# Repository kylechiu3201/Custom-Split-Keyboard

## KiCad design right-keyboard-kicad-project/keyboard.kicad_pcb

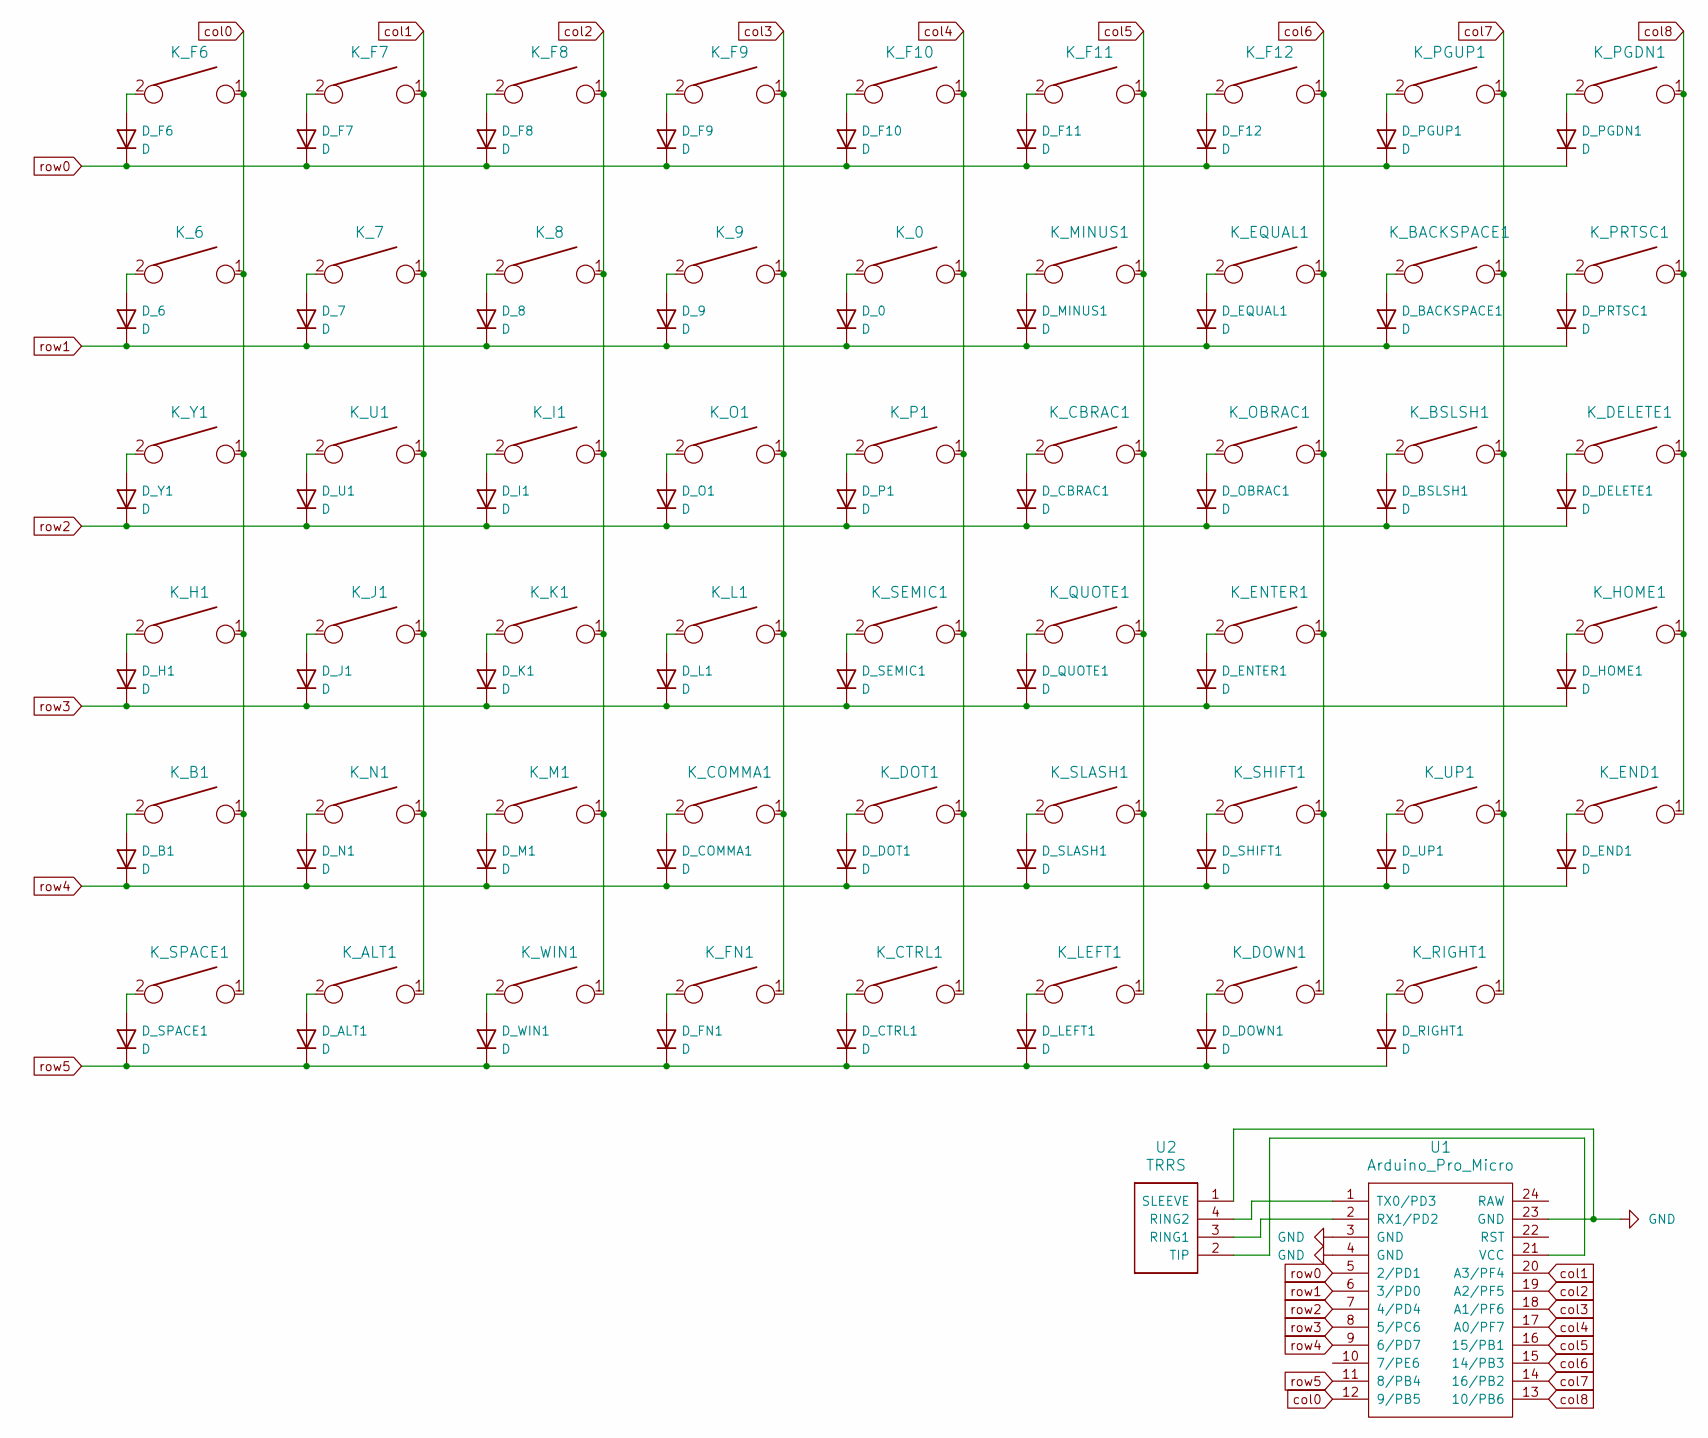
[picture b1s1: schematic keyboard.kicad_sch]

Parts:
D_0, D_6, D_7, D_8, D_9: D; D_SOD123_axial
D_ALT1: D; D_SOD123_axial
D_B1: D; D_SOD123_axial
D_BACKSPACE1: D; D_SOD123_axial
D_BSLSH1: D; D_SOD123_axial
D_CBRAC1: D; D_SOD123_axial
D_COMMA1: D; D_SOD123_axial
D_CTRL1: D; D_SOD123_axial
D_DELETE1: D; D_SOD123_axial
D_DOT1: D; D_SOD123_axial
D_DOWN1: D; D_SOD123_axial
D_END1: D; D_SOD123_axial
D_ENTER1: D; D_SOD123_axial
D_EQUAL1: D; D_SOD123_axial
D_F6, D_F7, D_F8, D_F9, D_F10, D_F11, D_F12: D; D_SOD123_axial
D_FN1: D; D_SOD123_axial
D_H1: D; D_SOD123_axial
D_HOME1: D; D_SOD123_axial
D_I1: D; D_SOD123_axial
D_J1: D; D_SOD123_axial
D_K1: D; D_SOD123_axial
D_L1: D; D_SOD123_axial
D_LEFT1: D; D_SOD123_axial
D_M1: D; D_SOD123_axial
D_MINUS1: D; D_SOD123_axial
D_N1: D; D_SOD123_axial
D_O1: D; D_SOD123_axial
D_OBRAC1: D; D_SOD123_axial
D_P1: D; D_SOD123_axial
D_PGDN1: D; D_SOD123_axial
D_PGUP1: D; D_SOD123_axial
D_PRTSC1: D; D_SOD123_axial
D_QUOTE1: D; D_SOD123_axial
D_RIGHT1: D; D_SOD123_axial
D_SEMIC1: D; D_SOD123_axial
D_SHIFT1: D; D_SOD123_axial
D_SLASH1: D; D_SOD123_axial
D_SPACE1: D; D_SOD123_axial
D_U1: D; D_SOD123_axial
D_UP1: D; D_SOD123_axial
D_WIN1: D; D_SOD123_axial
D_Y1: D; D_SOD123_axial
K_0, K_6, K_7, K_8, K_9: KEYSW; MXOnly-1U-Hotswap
K_ALT1: KEYSW; MXOnly-1U-Hotswap
K_B1: KEYSW; MXOnly-1U-Hotswap
K_BACKSPACE1: KEYSW; MXOnly-2U-Hotswap
K_BSLSH1: KEYSW; MXOnly-1.5U-Hotswap
K_CBRAC1: KEYSW; MXOnly-1U-Hotswap
K_COMMA1: KEYSW; MXOnly-1U-Hotswap
K_CTRL1: KEYSW; MXOnly-1U-Hotswap
K_DELETE1: KEYSW; MXOnly-1U-Hotswap
K_DOT1: KEYSW; MXOnly-1U-Hotswap
K_DOWN1: KEYSW; MXOnly-1U-Hotswap
K_END1: KEYSW; MXOnly-1U-Hotswap
K_ENTER1: KEYSW; MXOnly-2.25U-Hotswap
K_EQUAL1: KEYSW; MXOnly-1U-Hotswap
K_F6, K_F7, K_F8, K_F9, K_F10, K_F11, K_F12: KEYSW; MXOnly-1U-Hotswap
K_FN1: KEYSW; MXOnly-1U-Hotswap
K_H1: KEYSW; MXOnly-1U-Hotswap
K_HOME1: KEYSW; MXOnly-1U-Hotswap
K_I1: KEYSW; MXOnly-1U-Hotswap
K_J1: KEYSW; MXOnly-1U-Hotswap
K_K1: KEYSW; MXOnly-1U-Hotswap
K_L1: KEYSW; MXOnly-1U-Hotswap
K_LEFT1: KEYSW; MXOnly-1U-Hotswap
K_M1: KEYSW; MXOnly-1U-Hotswap
K_MINUS1: KEYSW; MXOnly-1U-Hotswap
K_N1: KEYSW; MXOnly-1U-Hotswap
K_O1: KEYSW; MXOnly-1U-Hotswap
K_OBRAC1: KEYSW; MXOnly-1U-Hotswap
K_P1: KEYSW; MXOnly-1U-Hotswap
K_PGDN1: KEYSW; MXOnly-1U-Hotswap
K_PGUP1: KEYSW; MXOnly-1U-Hotswap
K_PRTSC1: KEYSW; MXOnly-1U-Hotswap
K_QUOTE1: KEYSW; MXOnly-1U-Hotswap
K_RIGHT1: KEYSW; MXOnly-1U-Hotswap
K_SEMIC1: KEYSW; MXOnly-1U-Hotswap
K_SHIFT1: KEYSW; MXOnly-1.75U-Hotswap
K_SLASH1: KEYSW; MXOnly-1U-Hotswap
K_SPACE1: KEYSW; MXOnly-2.25U-Hotswap
K_U1: KEYSW; MXOnly-1U-Hotswap
K_UP1: KEYSW; MXOnly-1U-Hotswap
K_WIN1: KEYSW; MXOnly-1U-Hotswap
K_Y1: KEYSW; MXOnly-1U-Hotswap
U1: Arduino_Pro_Micro
U2: TRRS; TRRS_PJ-320A

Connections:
GND: U1.3 (GND), U1.4 (GND), U1.23 (GND), U2.1 (SLEEVE)
unnamed: D_0.2 (A), K_0.2
unnamed: D_6.2 (A), K_6.2
unnamed: D_7.2 (A), K_7.2
unnamed: D_8.2 (A), K_8.2
unnamed: D_9.2 (A), K_9.2
unnamed: D_ALT1.2 (A), K_ALT1.2
unnamed: D_B1.2 (A), K_B1.2
unnamed: D_BACKSPACE1.2 (A), K_BACKSPACE1.2
unnamed: D_BSLSH1.2 (A), K_BSLSH1.2
unnamed: D_CBRAC1.2 (A), K_CBRAC1.2
unnamed: D_COMMA1.2 (A), K_COMMA1.2
unnamed: D_CTRL1.2 (A), K_CTRL1.2
unnamed: D_DELETE1.2 (A), K_DELETE1.2
unnamed: D_DOT1.2 (A), K_DOT1.2
unnamed: D_DOWN1.2 (A), K_DOWN1.2
unnamed: D_END1.2 (A), K_END1.2
unnamed: D_ENTER1.2 (A), K_ENTER1.2
unnamed: D_EQUAL1.2 (A), K_EQUAL1.2
unnamed: D_F6.2 (A), K_F6.2
unnamed: D_F7.2 (A), K_F7.2
unnamed: D_F8.2 (A), K_F8.2
unnamed: D_F9.2 (A), K_F9.2
unnamed: D_F10.2 (A), K_F10.2
unnamed: D_F11.2 (A), K_F11.2
unnamed: D_F12.2 (A), K_F12.2
unnamed: D_FN1.2 (A), K_FN1.2
unnamed: D_H1.2 (A), K_H1.2
unnamed: D_HOME1.2 (A), K_HOME1.2
unnamed: D_I1.2 (A), K_I1.2
unnamed: D_J1.2 (A), K_J1.2
unnamed: D_K1.2 (A), K_K1.2
unnamed: D_L1.2 (A), K_L1.2
unnamed: D_LEFT1.2 (A), K_LEFT1.2
unnamed: D_M1.2 (A), K_M1.2
unnamed: D_MINUS1.2 (A), K_MINUS1.2
unnamed: D_N1.2 (A), K_N1.2
unnamed: D_O1.2 (A), K_O1.2
unnamed: D_OBRAC1.2 (A), K_OBRAC1.2
unnamed: D_P1.2 (A), K_P1.2
unnamed: D_PGDN1.2 (A), K_PGDN1.2
unnamed: D_PGUP1.2 (A), K_PGUP1.2
unnamed: D_PRTSC1.2 (A), K_PRTSC1.2
unnamed: D_QUOTE1.2 (A), K_QUOTE1.2
unnamed: D_RIGHT1.2 (A), K_RIGHT1.2
unnamed: D_SEMIC1.2 (A), K_SEMIC1.2
unnamed: D_SHIFT1.2 (A), K_SHIFT1.2
unnamed: D_SLASH1.2 (A), K_SLASH1.2
unnamed: D_SPACE1.2 (A), K_SPACE1.2
unnamed: D_U1.2 (A), K_U1.2
unnamed: D_UP1.2 (A), K_UP1.2
unnamed: D_WIN1.2 (A), K_WIN1.2
unnamed: D_Y1.2 (A), K_Y1.2
unnamed: U1.2 (RX1/PD2), U2.3 (RING1)
unnamed: U1.1 (TX0/PD3), U2.4 (RING2)
unnamed: U1.21 (VCC), U2.2 (TIP)
col0: K_6.1, K_B1.1, K_F6.1, K_H1.1, K_SPACE1.1, K_Y1.1, U1.12 (9/PB5)
col1: K_7.1, K_ALT1.1, K_F7.1, K_J1.1, K_N1.1, K_U1.1, U1.20 (A3/PF4)
col2: K_8.1, K_F8.1, K_I1.1, K_K1.1, K_M1.1, K_WIN1.1, U1.19 (A2/PF5)
col3: K_9.1, K_COMMA1.1, K_F9.1, K_FN1.1, K_L1.1, K_O1.1, U1.18 (A1/PF6)
col4: K_0.1, K_CTRL1.1, K_DOT1.1, K_F10.1, K_P1.1, K_SEMIC1.1, U1.17 (A0/PF7)
col5: K_CBRAC1.1, K_F11.1, K_LEFT1.1, K_MINUS1.1, K_QUOTE1.1, K_SLASH1.1, U1.16 (15/PB1)
col6: K_DOWN1.1, K_ENTER1.1, K_EQUAL1.1, K_F12.1, K_OBRAC1.1, K_SHIFT1.1, U1.15 (14/PB3)
col7: K_BACKSPACE1.1, K_BSLSH1.1, K_PGUP1.1, K_RIGHT1.1, K_UP1.1, U1.14 (16/PB2)
col8: K_DELETE1.1, K_END1.1, K_HOME1.1, K_PGDN1.1, K_PRTSC1.1, U1.13 (10/PB6)
row0: D_F6.1 (K), D_F7.1 (K), D_F8.1 (K), D_F9.1 (K), D_F10.1 (K), D_F11.1 (K), D_F12.1 (K), D_PGDN1.1 (K), D_PGUP1.1 (K), U1.5 (2/PD1)
row1: D_0.1 (K), D_6.1 (K), D_7.1 (K), D_8.1 (K), D_9.1 (K), D_BACKSPACE1.1 (K), D_EQUAL1.1 (K), D_MINUS1.1 (K), D_PRTSC1.1 (K), U1.6 (3/PD0)
row2: D_BSLSH1.1 (K), D_CBRAC1.1 (K), D_DELETE1.1 (K), D_I1.1 (K), D_O1.1 (K), D_OBRAC1.1 (K), D_P1.1 (K), D_U1.1 (K), D_Y1.1 (K), U1.7 (4/PD4)
row3: D_ENTER1.1 (K), D_H1.1 (K), D_HOME1.1 (K), D_J1.1 (K), D_K1.1 (K), D_L1.1 (K), D_QUOTE1.1 (K), D_SEMIC1.1 (K), U1.8 (5/PC6)
row4: D_B1.1 (K), D_COMMA1.1 (K), D_DOT1.1 (K), D_END1.1 (K), D_M1.1 (K), D_N1.1 (K), D_SHIFT1.1 (K), D_SLASH1.1 (K), D_UP1.1 (K), U1.9 (6/PD7)
row5: D_ALT1.1 (K), D_CTRL1.1 (K), D_DOWN1.1 (K), D_FN1.1 (K), D_LEFT1.1 (K), D_RIGHT1.1 (K), D_SPACE1.1 (K), D_WIN1.1 (K), U1.11 (8/PB4)

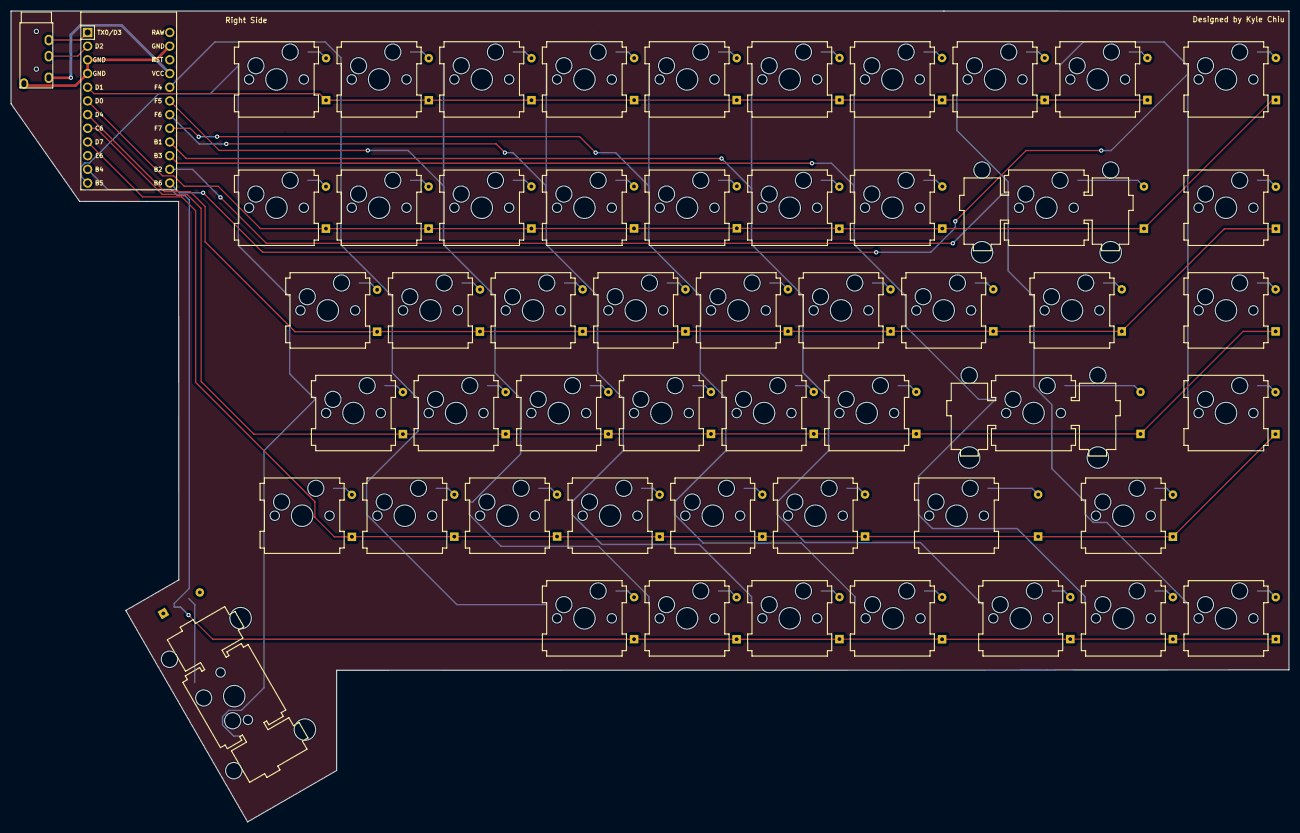
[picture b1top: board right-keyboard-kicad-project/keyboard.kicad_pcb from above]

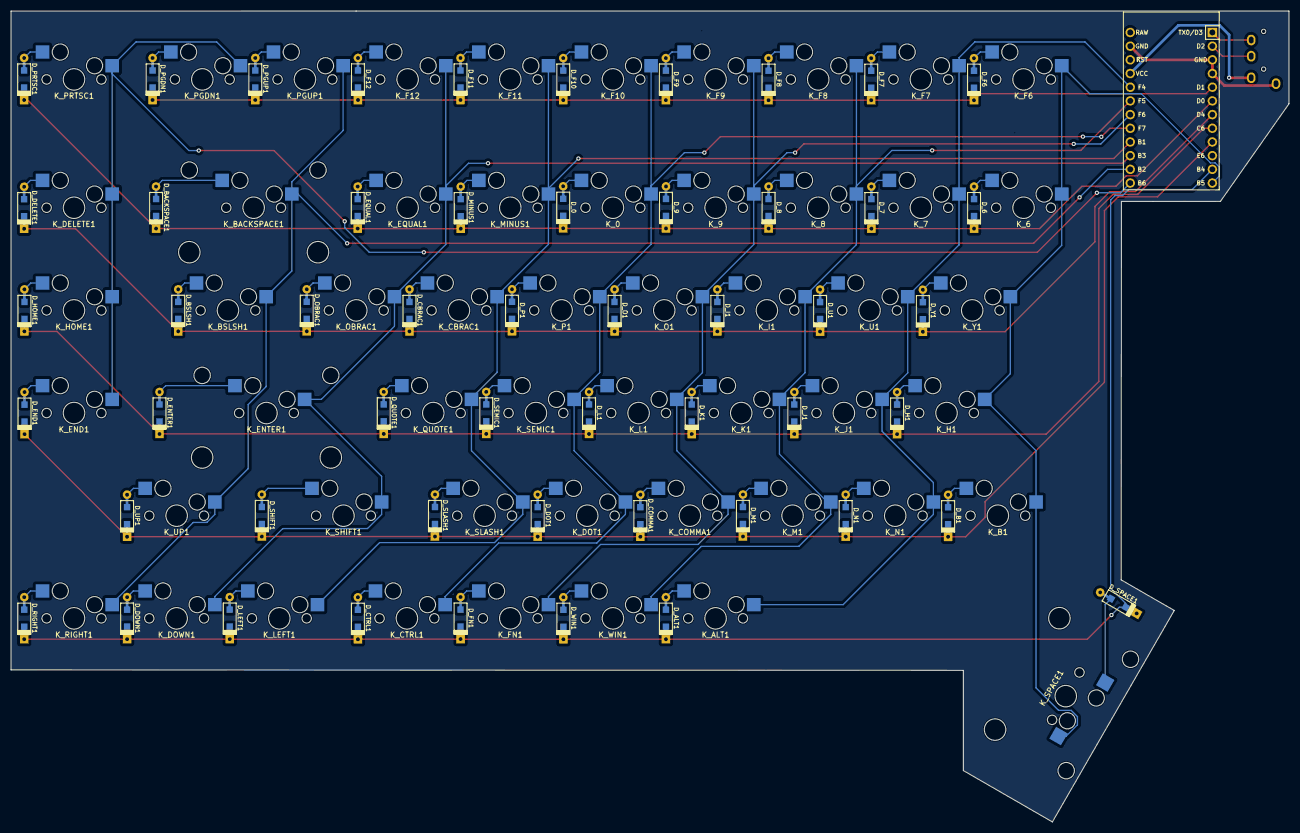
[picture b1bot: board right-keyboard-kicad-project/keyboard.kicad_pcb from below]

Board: 2 copper layers, 237.1 x 150.5 mm, 106 parts (52 on the bottom side), 71 nets.

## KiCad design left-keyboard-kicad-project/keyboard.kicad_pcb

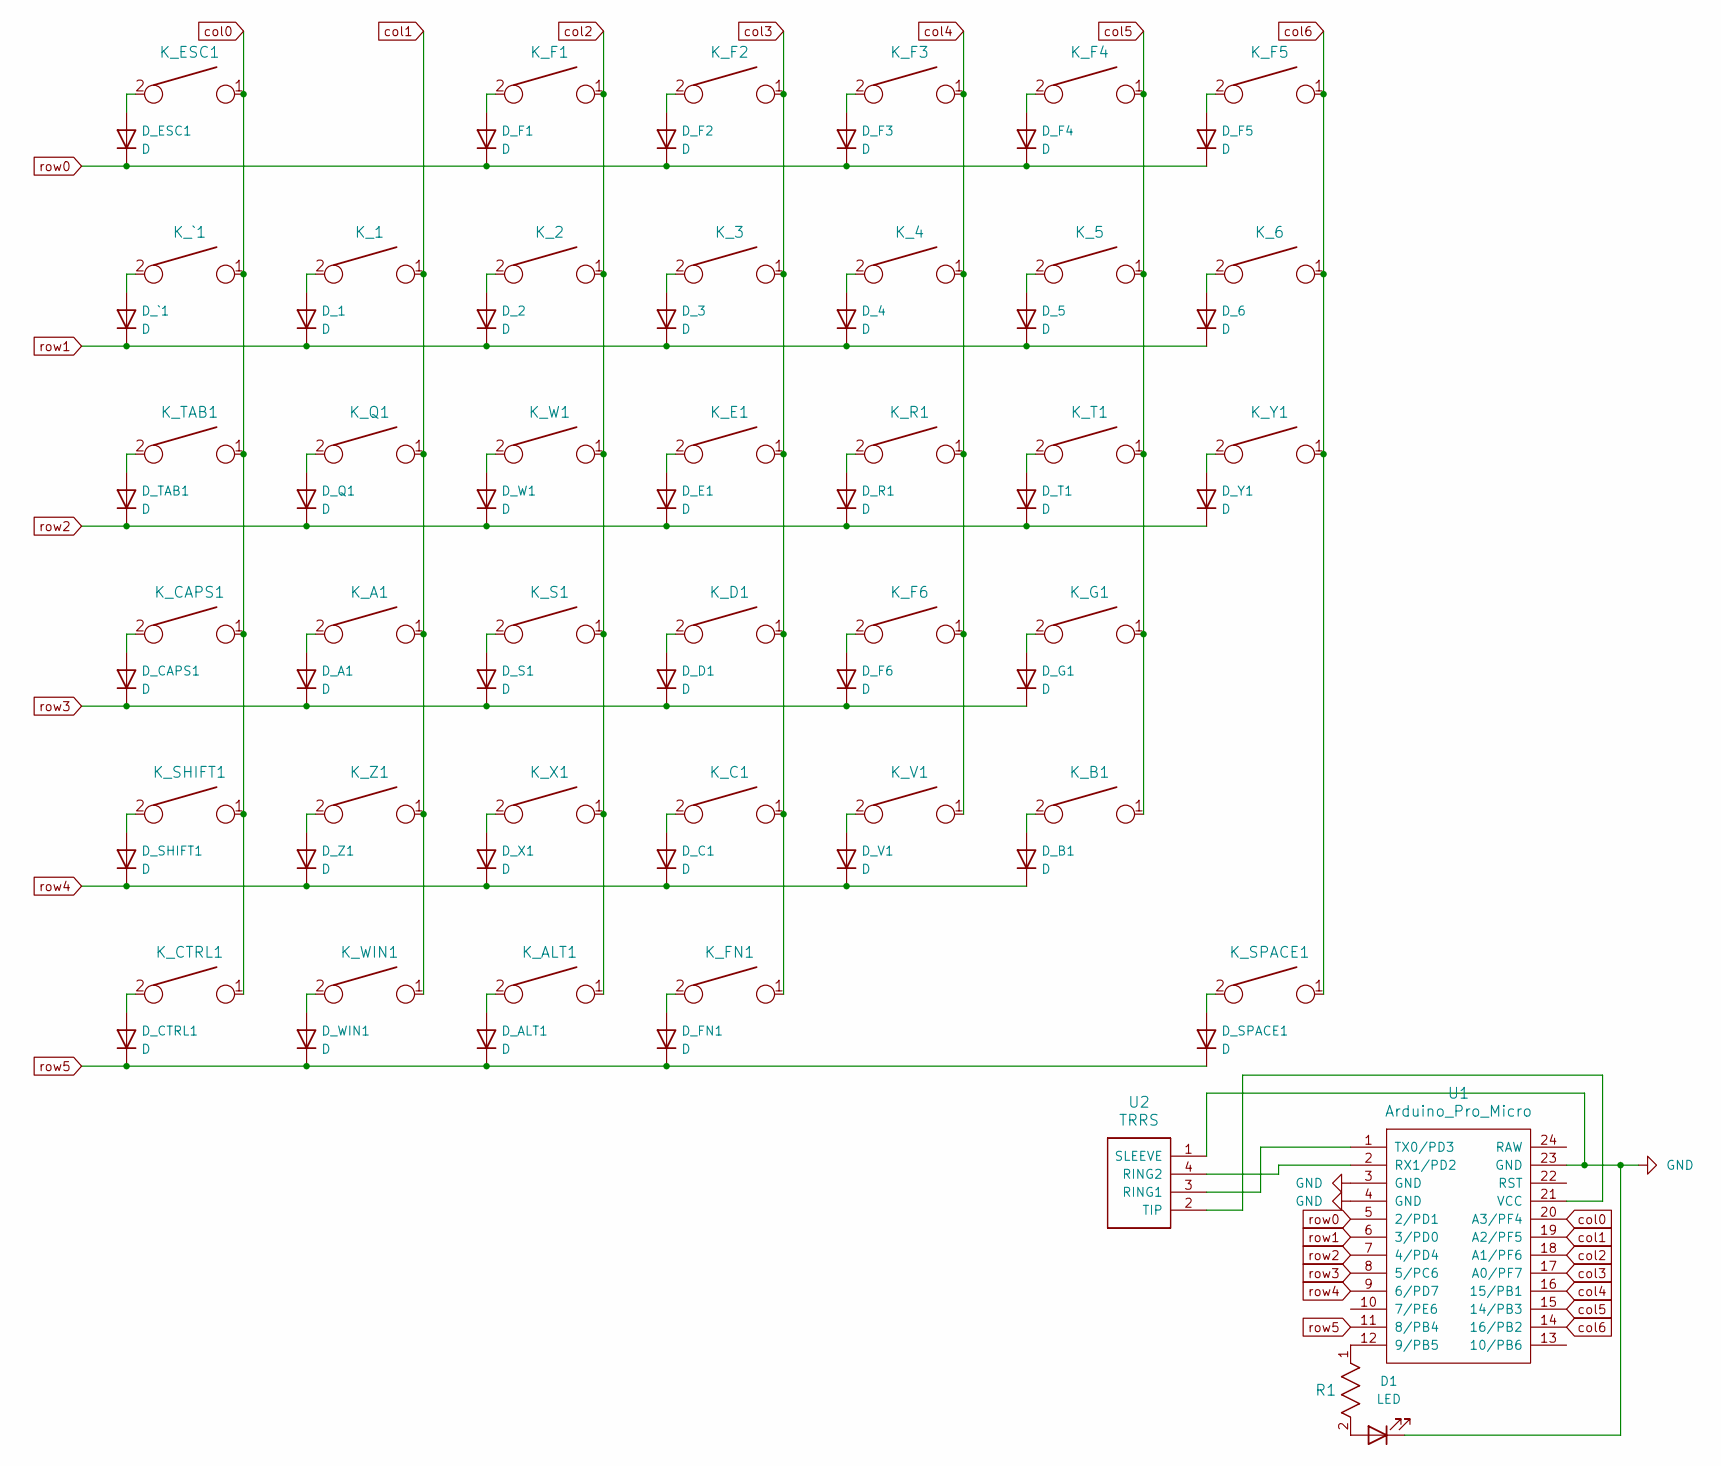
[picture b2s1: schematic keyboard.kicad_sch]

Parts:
D1: LED; LED_CREE_MX6
D_1, D_2, D_3, D_4, D_5, D_6: D; D_SOD123_axial
D_A1: D; D_SOD123_axial
D_ALT1: D; D_SOD123_axial
D_B1: D; D_SOD123_axial
D_C1: D; D_SOD123_axial
D_CAPS1: D; D_SOD123_axial
D_CTRL1: D; D_SOD123_axial
D_D1: D; D_SOD123_axial
D_E1: D; D_SOD123_axial
D_ESC1: D; D_SOD123_axial
D_F1, D_F2, D_F3, D_F4, D_F5, D_F6: D; D_SOD123_axial
D_FN1: D; D_SOD123_axial
D_G1: D; D_SOD123_axial
D_Q1: D; D_SOD123_axial
D_R1: D; D_SOD123_axial
D_S1: D; D_SOD123_axial
D_SHIFT1: D; D_SOD123_axial
D_SPACE1: D; D_SOD123_axial
D_T1: D; D_SOD123_axial
D_TAB1: D; D_SOD123_axial
D_V1: D; D_SOD123_axial
D_W1: D; D_SOD123_axial
D_WIN1: D; D_SOD123_axial
D_X1: D; D_SOD123_axial
D_Y1: D; D_SOD123_axial
D_Z1: D; D_SOD123_axial
D_`1: D; D_SOD123_axial
K_1, K_2, K_3, K_4, K_5, K_6: KEYSW; MXOnly-1U-Hotswap
K_A1: KEYSW; MXOnly-1U-Hotswap
K_ALT1: KEYSW; MXOnly-1.25U-Hotswap
K_B1: KEYSW; MXOnly-1U-Hotswap
K_C1: KEYSW; MXOnly-1U-Hotswap
K_CAPS1: KEYSW; MXOnly-1.75U-Hotswap
K_CTRL1: KEYSW; MXOnly-1.25U-Hotswap
K_D1: KEYSW; MXOnly-1U-Hotswap
K_E1: KEYSW; MXOnly-1U-Hotswap
K_ESC1: KEYSW; MXOnly-1U-Hotswap
K_F1, K_F2, K_F3, K_F4, K_F5, K_F6: KEYSW; MXOnly-1U-Hotswap
K_FN1: KEYSW; MXOnly-1.25U-Hotswap
K_G1: KEYSW; MXOnly-1U-Hotswap
K_Q1: KEYSW; MXOnly-1U-Hotswap
K_R1: KEYSW; MXOnly-1U-Hotswap
K_S1: KEYSW; MXOnly-1U-Hotswap
K_SHIFT1: KEYSW; MXOnly-2.25U-Hotswap
K_SPACE1: KEYSW; MXOnly-2.25U-Hotswap
K_T1: KEYSW; MXOnly-1U-Hotswap
K_TAB1: KEYSW; MXOnly-1.5U-Hotswap
K_V1: KEYSW; MXOnly-1U-Hotswap
K_W1: KEYSW; MXOnly-1U-Hotswap
K_WIN1: KEYSW; MXOnly-1.25U-Hotswap
K_X1: KEYSW; MXOnly-1U-Hotswap
K_Y1: KEYSW; MXOnly-1U-Hotswap
K_Z1: KEYSW; MXOnly-1U-Hotswap
K_`1: KEYSW; MXOnly-1U-Hotswap
R1: R_0805_2012Metric_Pad1.20x1.40mm_HandSolder
U1: Arduino_Pro_Micro
U2: TRRS; TRRS_PJ-320A

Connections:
GND: D1.1 (K), U1.3 (GND), U1.4 (GND), U1.23 (GND), U2.1 (SLEEVE)
unnamed: D1.2 (A), R1.2
unnamed: D_1.2 (A), K_1.2
unnamed: D_2.2 (A), K_2.2
unnamed: D_3.2 (A), K_3.2
unnamed: D_4.2 (A), K_4.2
unnamed: D_5.2 (A), K_5.2
unnamed: D_6.2 (A), K_6.2
unnamed: D_A1.2 (A), K_A1.2
unnamed: D_ALT1.2 (A), K_ALT1.2
unnamed: D_B1.2 (A), K_B1.2
unnamed: D_C1.2 (A), K_C1.2
unnamed: D_CAPS1.2 (A), K_CAPS1.2
unnamed: D_CTRL1.2 (A), K_CTRL1.2
unnamed: D_D1.2 (A), K_D1.2
unnamed: D_E1.2 (A), K_E1.2
unnamed: D_ESC1.2 (A), K_ESC1.2
unnamed: D_F1.2 (A), K_F1.2
unnamed: D_F2.2 (A), K_F2.2
unnamed: D_F3.2 (A), K_F3.2
unnamed: D_F4.2 (A), K_F4.2
unnamed: D_F5.2 (A), K_F5.2
unnamed: D_F6.2 (A), K_F6.2
unnamed: D_FN1.2 (A), K_FN1.2
unnamed: D_G1.2 (A), K_G1.2
unnamed: D_Q1.2 (A), K_Q1.2
unnamed: D_R1.2 (A), K_R1.2
unnamed: D_S1.2 (A), K_S1.2
unnamed: D_SHIFT1.2 (A), K_SHIFT1.2
unnamed: D_SPACE1.2 (A), K_SPACE1.2
unnamed: D_T1.2 (A), K_T1.2
unnamed: D_TAB1.2 (A), K_TAB1.2
unnamed: D_V1.2 (A), K_V1.2
unnamed: D_W1.2 (A), K_W1.2
unnamed: D_WIN1.2 (A), K_WIN1.2
unnamed: D_X1.2 (A), K_X1.2
unnamed: D_Y1.2 (A), K_Y1.2
unnamed: D_Z1.2 (A), K_Z1.2
unnamed: D_`1.2 (A), K_`1.2
unnamed: R1.1, U1.12 (9/PB5)
unnamed: U1.2 (RX1/PD2), U2.4 (RING2)
unnamed: U1.1 (TX0/PD3), U2.3 (RING1)
unnamed: U1.21 (VCC), U2.2 (TIP)
col0: K_CAPS1.1, K_CTRL1.1, K_ESC1.1, K_SHIFT1.1, K_TAB1.1, K_`1.1, U1.20 (A3/PF4)
col1: K_1.1, K_A1.1, K_Q1.1, K_WIN1.1, K_Z1.1, U1.19 (A2/PF5)
col2: K_2.1, K_ALT1.1, K_F1.1, K_S1.1, K_W1.1, K_X1.1, U1.18 (A1/PF6)
col3: K_3.1, K_C1.1, K_D1.1, K_E1.1, K_F2.1, K_FN1.1, U1.17 (A0/PF7)
col4: K_4.1, K_F3.1, K_F6.1, K_R1.1, K_V1.1, U1.16 (15/PB1)
col5: K_5.1, K_B1.1, K_F4.1, K_G1.1, K_T1.1, U1.15 (14/PB3)
col6: K_6.1, K_F5.1, K_SPACE1.1, K_Y1.1, U1.14 (16/PB2)
row0: D_ESC1.1 (K), D_F1.1 (K), D_F2.1 (K), D_F3.1 (K), D_F4.1 (K), D_F5.1 (K), U1.5 (2/PD1)
row1: D_1.1 (K), D_2.1 (K), D_3.1 (K), D_4.1 (K), D_5.1 (K), D_6.1 (K), D_`1.1 (K), U1.6 (3/PD0)
row2: D_E1.1 (K), D_Q1.1 (K), D_R1.1 (K), D_T1.1 (K), D_TAB1.1 (K), D_W1.1 (K), D_Y1.1 (K), U1.7 (4/PD4)
row3: D_A1.1 (K), D_CAPS1.1 (K), D_D1.1 (K), D_F6.1 (K), D_G1.1 (K), D_S1.1 (K), U1.8 (5/PC6)
row4: D_B1.1 (K), D_C1.1 (K), D_SHIFT1.1 (K), D_V1.1 (K), D_X1.1 (K), D_Z1.1 (K), U1.9 (6/PD7)
row5: D_ALT1.1 (K), D_CTRL1.1 (K), D_FN1.1 (K), D_SPACE1.1 (K), D_WIN1.1 (K), U1.11 (8/PB4)

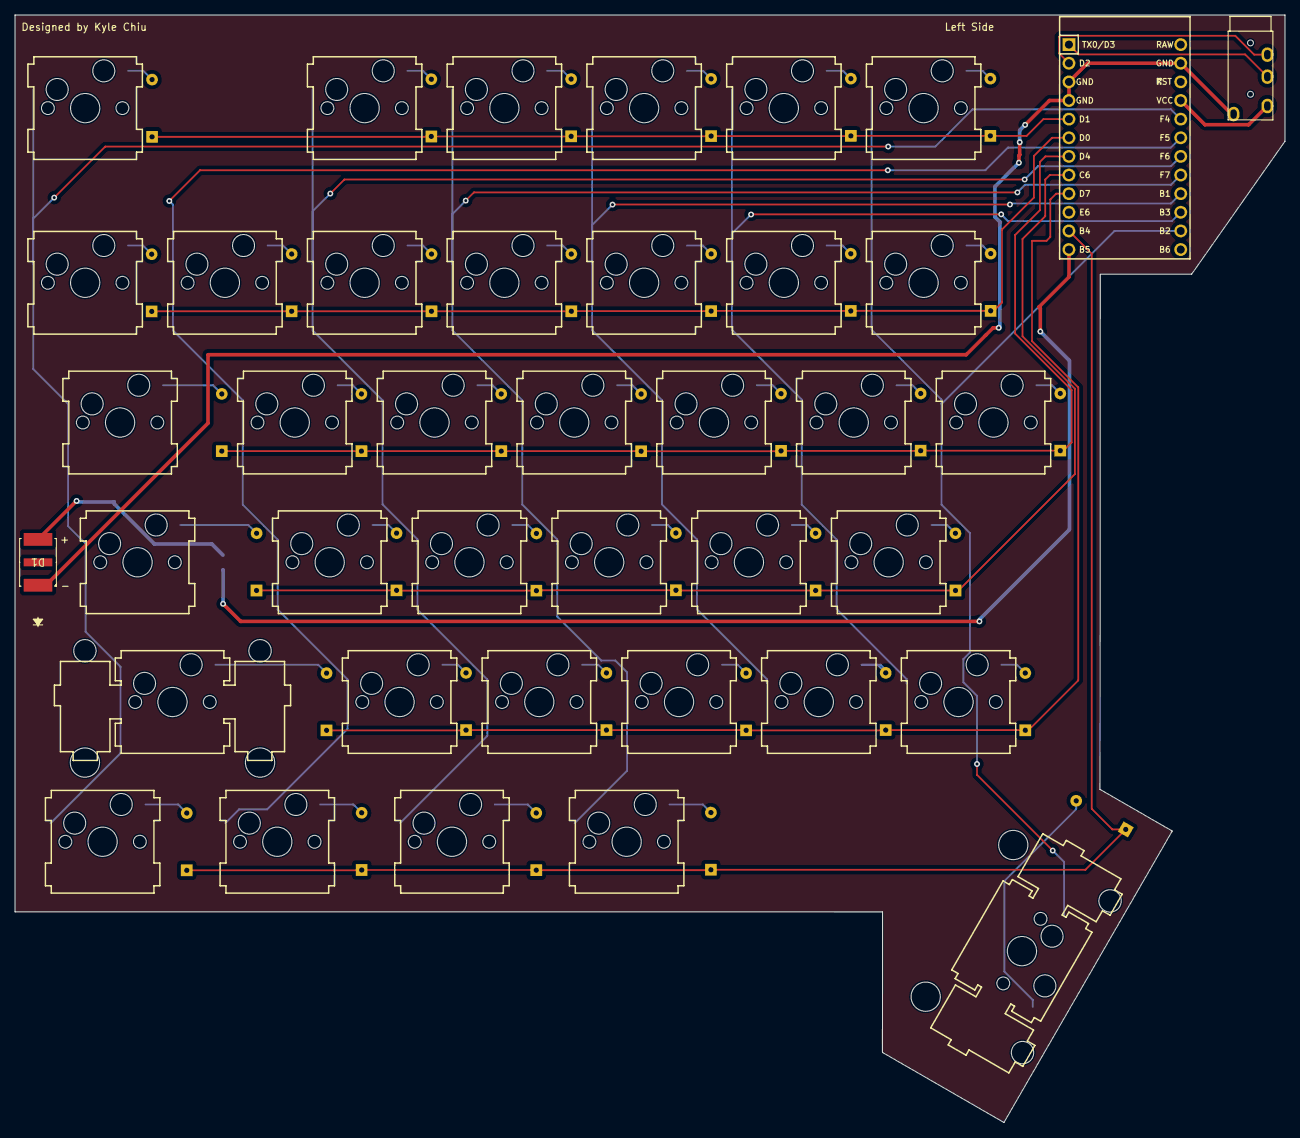
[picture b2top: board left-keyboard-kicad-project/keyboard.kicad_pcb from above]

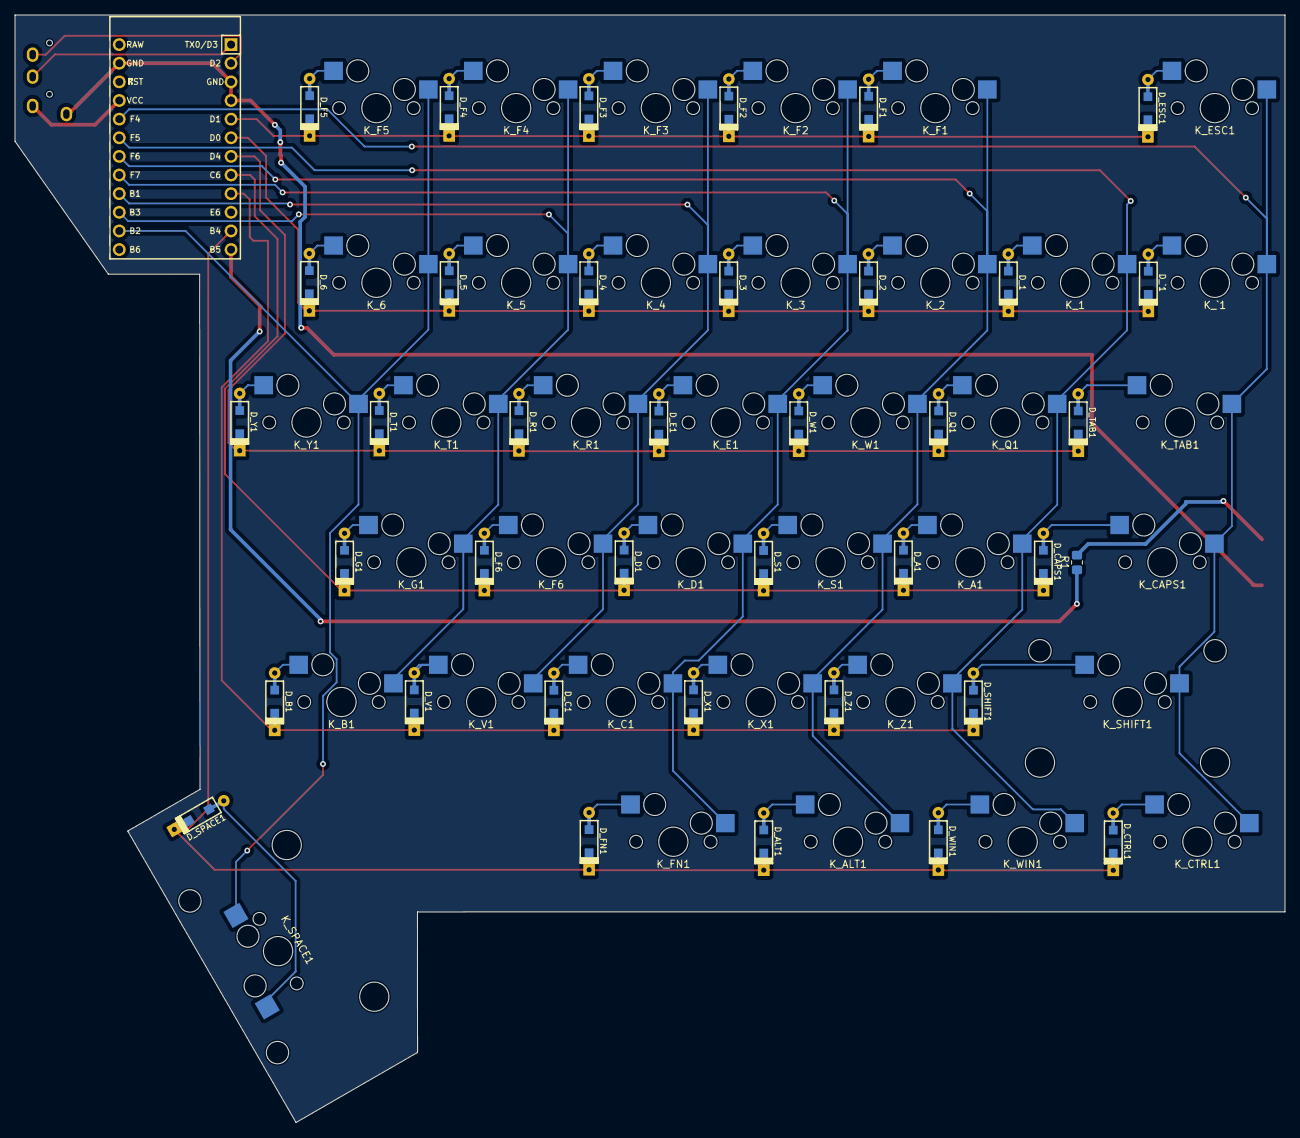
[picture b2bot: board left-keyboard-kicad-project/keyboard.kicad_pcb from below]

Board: 2 copper layers, 173.1 x 151.0 mm, 78 parts (38 on the bottom side), 56 nets.

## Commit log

2023-12-19 add README.md
2023-12-19 finished left keyboard
2023-12-19 update left keyboard to have slightly shifted LED
2023-12-19 update left keyboard
2023-12-20 added hotswap sockets
2023-12-20 Moved MCU and redid board cuts
2023-12-20 Updated gerber.zip
2023-12-20 started right keyboard Kicad project
2023-12-20 Redid right keyboard firmware wiring and started right keyboard Kicad project
2023-12-20 Completed placing switches and some diodes for right side
2023-12-20 Updated track width for VCC to be thicker
2023-12-20 Finished right side of keyboard
2023-12-20 Generated gerber files for both left and right keyboards
